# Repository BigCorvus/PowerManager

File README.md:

# PowerManager

Small battery and power manager PCB based on a previously designed charger+LDO board. Even breaks out the USB data pins and can therefore be integrated into any battery-powered project. Besides the ever-useful sot-23 Lithium charger (MCP73831) and 3,3V LDO this new version has additional features: MCU-controlled power latching using a pushbutton and a BQ27441-G1A fuel gauge with current sensing capability. Various LDO models can be used depending on current requirements and quiescent current. They should match the footprint and have an active high enable pin. Examples are AP2112 or XC6215...  
The BTN_TO_MCU pin is an output which is high as soon as long as the button is pressed. It can beused to control stuff inside your application code. The PHOLD pin is an input which has to be pulled up by the microcontroller as soon as possible. Actually this should be the first thing your code does. After the button is pushed the EN pin of the LDO is pulled up for a short period, which depends on the capacitor. 10µF give you about 2 seconds to react.

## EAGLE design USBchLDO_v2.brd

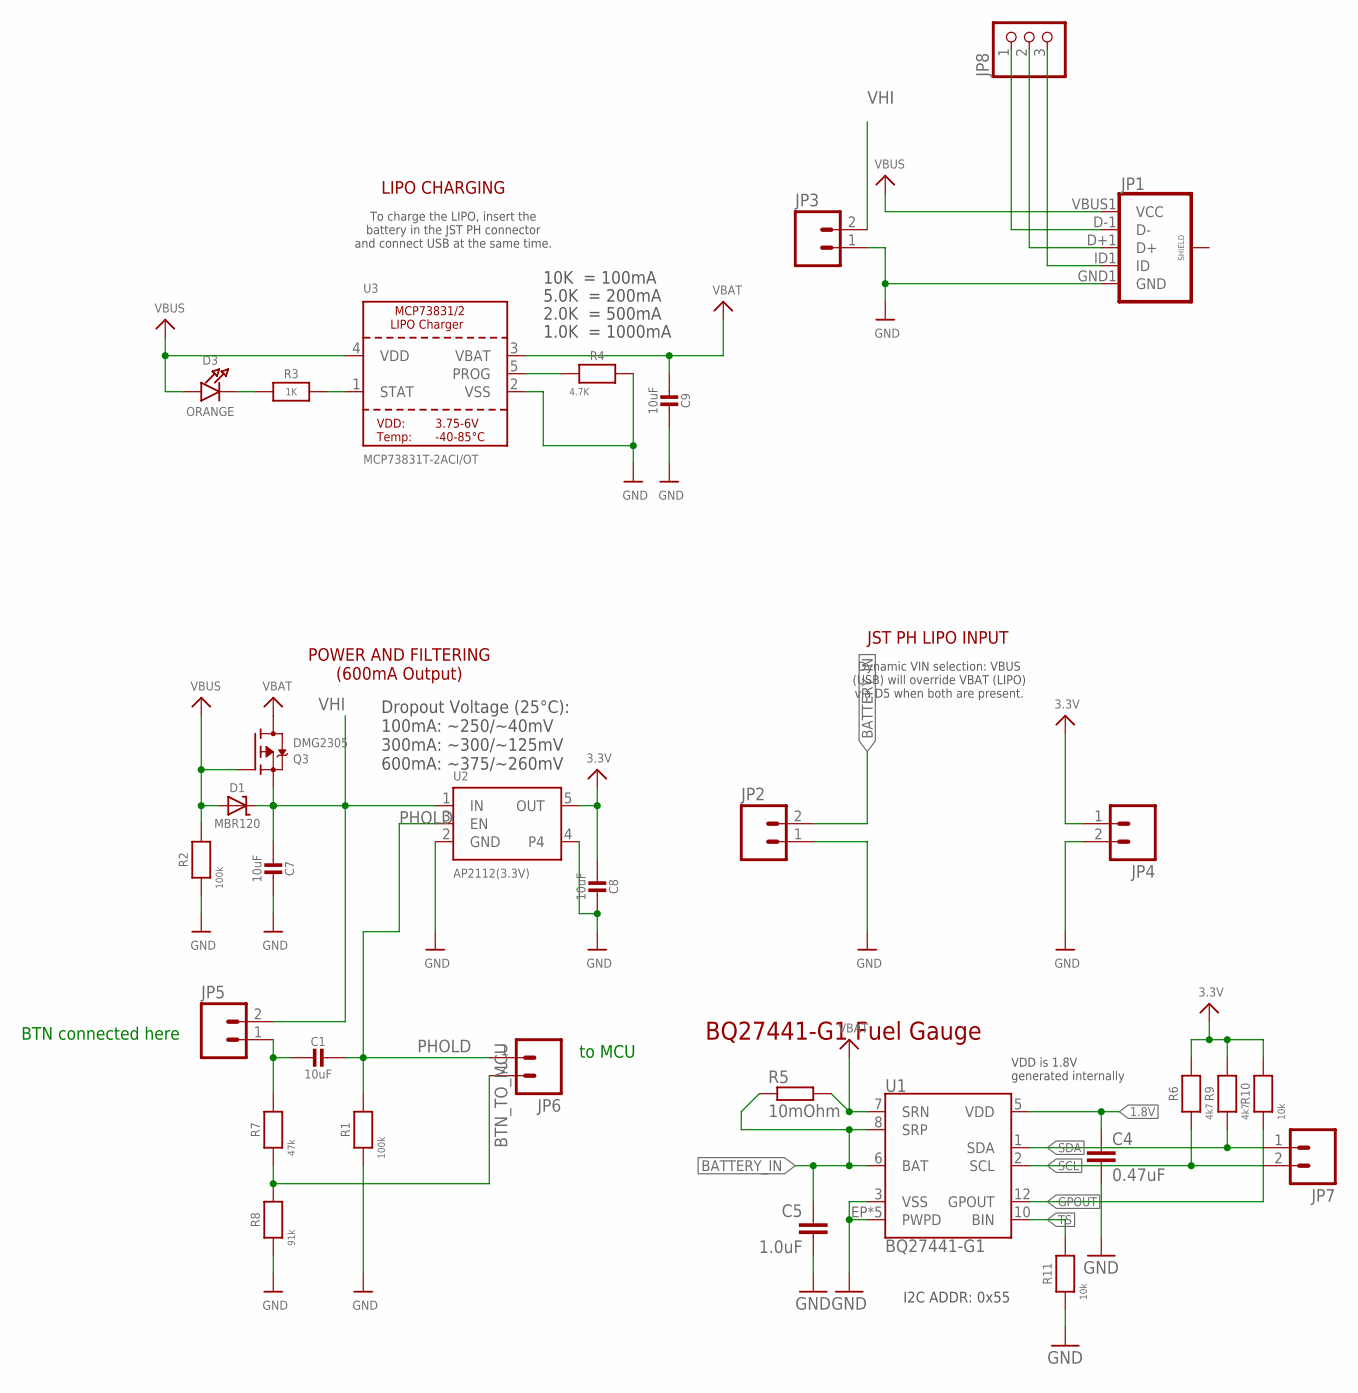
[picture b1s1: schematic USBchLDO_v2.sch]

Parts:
C1, C7, C8, C9: 10uF; 0805-NO
C4: 0.47uF; 0603-CAP
C5: 1.0uF; 0603-CAP
D1: MBR120; SOD-123
D3: ORANGE; CHIPLED_0805_NOOUTLINE
JP1: USB_MICROB_PLUGCONN-11752; USB-B-MICRO-SMD_V03
JP2, JP3, JP4, JP5, JP6, JP7: M02PTH; 1X02
JP8: PINHD-1X3; 1X03
Q3: DMG2305; SOT23-R
R1, R2: 100k; 0603-NO
R3: 1K; 0603-NO
R4: 4.7K; 0603-NO
R5: 10mOhm; R0805
R6, R9: 4k7; 0603-NO
R7: 47k; 0603-NO
R8: 91k; 0603-NO
R10, R11: 10k; 0603-NO
U1: BQ27441-G1; PDSO-N12
U2: AP2112(3.3V); SOT23-5
U3: MCP73831T-2ACI/OT; SOT23-5

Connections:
1.8V: C4.1, U1.5 (VDD)
3.3V: C8.2, JP4.1, R6.2, R9.2, R10.2, U2.5 (OUT)
BATTERY_IN: C5.1, JP2.2, R5.1, U1.6 (BAT), U1.8 (SRP)
BTN_TO_MCU: JP6.2, R7.1, R8.2
B_IN: C1.2, JP5.1, R7.2
GND: C4.2, C5.2, C7.1, C8.1, C9.1, JP1.GND1 (GND), JP2.1, JP3.1, JP4.2, R1.1, R2.1, R4.2, R8.1, R11.1, U1.3 (VSS), U1.EP (PWPD), U1.EP1 (PWPD), U1.EP2 (PWPD), U1.EP3 (PWPD), U1.EP4 (PWPD), U2.2 (GND), U2.4, U3.2 (VSS)
GPOUT: R10.1, U1.12 (GPOUT)
unnamed: D3.C, R3.1
unnamed: JP1.ID1 (ID), JP8.3
unnamed: R3.2, U3.1 (STAT)
unnamed: R4.1, U3.5 (PROG)
PHOLD: C1.1, JP6.1, R1.2, U2.3 (EN)
SCL: JP7.2, R6.1, U1.2 (SCL)
SDA: JP7.1, R9.1, U1.1 (SDA)
TS: R11.2, U1.10 (BIN)
USB_N: JP1.D-1 (D-), JP8.1
USB_P: JP1.D+1 (D+), JP8.2
VBAT: C9.2, Q3.3 (D), R5.2, U1.7 (SRN), U3.3 (VBAT)
VBUS: D1.A, D3.A, JP1.VBUS1 (VCC), Q3.1 (G), R2.2, U3.4 (VDD)
VHI: C7.2, D1.C, JP3.2, JP5.2, Q3.2 (S), U2.1 (IN)

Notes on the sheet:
POWER AND FILTERING (600mA Output)
Dropout Voltage (25°C): 100mA: ~250/~40mV 300mA: ~300/~125mV 600mA: ~375/~260mV
10K = 100mA
5.0K = 200mA
2.0K = 500mA
1.0K = 1000mA
LIPO CHARGING
To charge the LIPO, insert the battery in the JST PH connector and connect USB at the same time.
JST PH LIPO INPUT
Dynamic VIN selection: VBUS (USB) will override VBAT (LIPO) via D5 when both are present.
BQ27441-G1 Fuel Gauge
VDD is 1.8V generated internally
I2C ADDR: 0x55
to MCU
BTN connected here

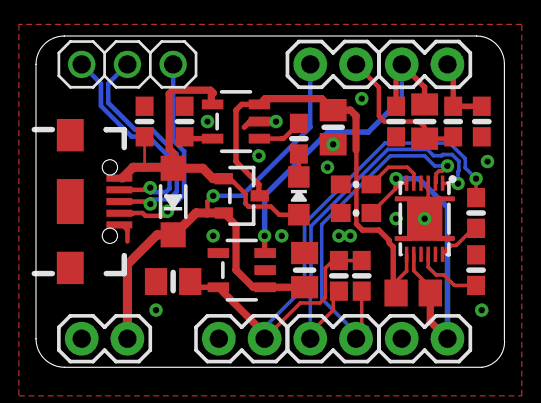
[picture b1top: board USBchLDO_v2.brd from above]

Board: 2 copper layers, 26.0 x 18.4 mm, 31 parts (0 on the bottom side), 20 nets.

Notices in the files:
parts and their libraries:
microbuilder: This work is placed in the public domain, and may be freely used for commercial and non-commercial work with the following conditions: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
SparkFun-Connectors: Licensing: Creative Commons ShareAlike 4.0 International - https://creativecommons.org/licenses/by-sa/4.0
